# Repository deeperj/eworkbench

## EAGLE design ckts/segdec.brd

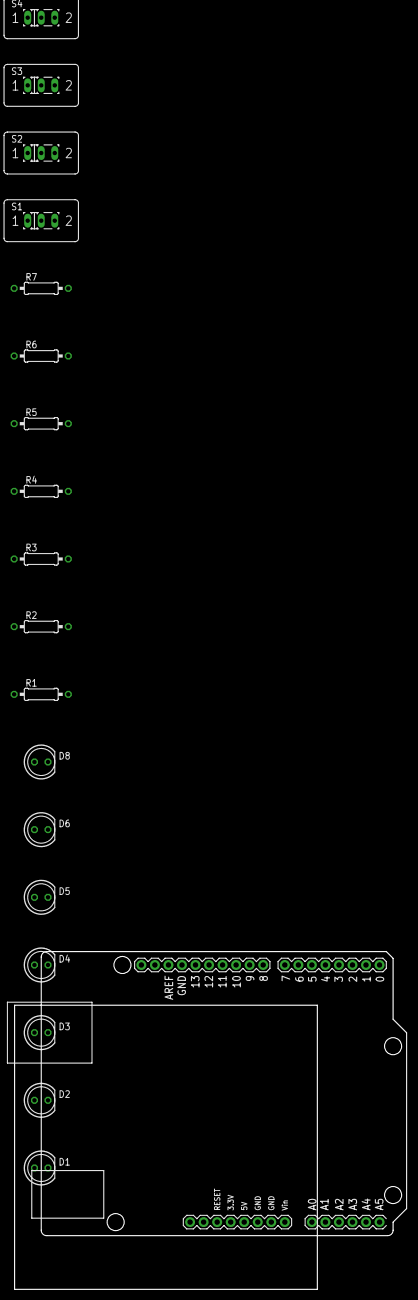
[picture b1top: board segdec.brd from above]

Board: 2 copper layers, 73.6 x 63.4 mm, 19 parts (0 on the bottom side), 20 nets, no tracks yet.

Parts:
D1, D2, D3, D4, D5, D6, D8: LED5MM
R1, R2, R3, R4, R5, R6, R7: 1k‎Ω; 0207/10
S1, S2, S3, S4: M251
U1: ARDUINO_UNO

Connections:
unnamed: D1.A, R1.2
unnamed: D4.A, R4.2
unnamed: S1.2, U1.13
unnamed: S2.2, U1.12
unnamed: S3.2, U1.11
unnamed: S4.2, U1.10
unnamed: S1.3, S2.3, S3.3, S4.3, U1.5V
unnamed: D8.A, R7.2
unnamed: D6.A, R6.2
unnamed: D5.A, R5.2
unnamed: D3.A, R3.2
unnamed: D2.A, R2.2
unnamed: D1.K, S1.1, S2.1, S3.1, S4.1, U1.GND.
unnamed: R7.1, U1.1
unnamed: R6.1, U1.2
unnamed: R5.1, U1.3
unnamed: R4.1, U1.4
unnamed: R3.1, U1.5
unnamed: R2.1, U1.6
unnamed: R1.1, U1.7

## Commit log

2019-03-09 sw_l053
2019-03-09 oscilloscope2.tft
2019-03-20 scomm
2019-03-20 working serial monitor driver
2019-03-21 std peripherals
2019-03-21 ignored help files
2019-03-21 serial comms complete
2019-03-21 TIMER funcs
2019-03-21 not quite sure what this is
2019-03-22 pause and capture implementation
2019-04-15 news00
2019-04-21 phantom zone
2019-04-21 superlists2
2019-04-21 ftesting
2019-04-22 agro
2019-04-22 dbpy00
2019-04-22 django_gen
2019-04-22 db00
2019-04-22 db01
2019-04-23 db02
2019-04-23 db03
2019-04-23 db04 dbpyv2
2019-04-23 dbx2yaml mgen refactor
2019-04-23 behave and stuff
2019-04-23 db04
2019-04-23 db05
2019-04-24 will cause a conflict
2019-04-24 modified beyond repair
2019-04-24 not a lot
2019-04-24 behave changes
2019-04-24 Agro app run
2019-04-24 not sure anymore
2019-05-01 ubl stuff
2019-05-01 python settings
2019-05-01 new bahave+models
2019-05-05 mods
2019-05-05 other mods
2019-05-09 forms
2019-05-13 tdel
2019-05-13 gitignore
2019-05-14 macsolutions
2019-05-15 gitck
2019-05-15 pvdata?
2019-05-15 mac2ann
2019-05-16 accuracy
2019-05-16 vsc mac python settings
2019-05-26 abcjade
2019-05-26 animate
2019-05-29 del macsol+agro_old
2019-05-29 award tender abcjade
2019-05-29 gignore
2019-05-29 gignore2
2019-05-29 what
2019-05-29 gignore3
2019-05-29 sync
2019-05-30 agro old
2019-06-05 weva
2019-06-07 design home
2019-06-11 element-vue-example
2019-06-23 mpp00
2019-06-23 ubl?
2019-09-07 whatever
2019-11-18 spice
2019-11-18 Bump lodash from 4.17.11 to 4.17.15 in /newngp/abcjade
    Bumps [lodash](https://github.com/lodash/lodash) from 4.17.11 to 4.17.15.
    - [Release notes](https://github.com/lodash/lodash/releases)
    - [Commits](https://github.com/lodash/lodash/compare/4.17.11...4.17.15)
2019-11-18 Bump mixin-deep from 1.3.1 to 1.3.2 in /newngp/abcjade
    Bumps [mixin-deep](https://github.com/jonschlinkert/mixin-deep) from 1.3.1 to 1.3.2.
    - [Release notes](https://github.com/jonschlinkert/mixin-deep/releases)
    - [Commits](https://github.com/jonschlinkert/mixin-deep/compare/1.3.1...1.3.2)
2019-12-28 Bump handlebars from 4.1.2 to 4.5.3 in /newngp/abcjade
    Bumps [handlebars](https://github.com/wycats/handlebars.js) from 4.1.2 to 4.5.3.
    - [Release notes](https://github.com/wycats/handlebars.js/releases)
    - [Changelog](https://github.com/wycats/handlebars.js/blob/master/release-notes.md)
    - [Commits](https://github.com/wycats/handlebars.js/compare/v4.1.2...v4.5.3)
2020-02-12 Bump django from 2.0 to 2.2.10 in /ftesting
    Bumps [django](https://github.com/django/django) from 2.0 to 2.2.10.
    - [Release notes](https://github.com/django/django/releases)
    - [Commits](https://github.com/django/django/compare/2.0...2.2.10)
2020-03-14 Bump acorn from 6.1.1 to 6.4.1 in /newngp/abcjade
    Bumps [acorn](https://github.com/acornjs/acorn) from 6.1.1 to 6.4.1.
    - [Release notes](https://github.com/acornjs/acorn/releases)
    - [Commits](https://github.com/acornjs/acorn/compare/6.1.1...6.4.1)
2020-04-16 Bump https-proxy-agent from 2.2.1 to 2.2.4 in /newngp/abcjade
    Bumps [https-proxy-agent](https://github.com/TooTallNate/node-https-proxy-agent) from 2.2.1 to 2.2.4.
    - [Release notes](https://github.com/TooTallNate/node-https-proxy-agent/releases)
    - [Commits](https://github.com/TooTallNate/node-https-proxy-agent/compare/2.2.1...2.2.4)
2020-06-05 Bump django from 2.0 to 2.2.13 in /ftesting
    Bumps [django](https://github.com/django/django) from 2.0 to 2.2.13.
    - [Release notes](https://github.com/django/django/releases)
    - [Commits](https://github.com/django/django/compare/2.0...2.2.13)
2020-06-06 Bump websocket-extensions from 0.1.3 to 0.1.4 in /newngp/abcjade
    Bumps [websocket-extensions](https://github.com/faye/websocket-extensions-node) from 0.1.3 to 0.1.4.
    - [Release notes](https://github.com/faye/websocket-extensions-node/releases)
    - [Changelog](https://github.com/faye/websocket-extensions-node/blob/master/CHANGELOG.md)
    - [Commits](https://github.com/faye/websocket-extensions-node/compare/0.1.3...0.1.4)
2020-07-17 Bump lodash from 4.17.11 to 4.17.19 in /newngp/abcjade
    Bumps [lodash](https://github.com/lodash/lodash) from 4.17.11 to 4.17.19.
    - [Release notes](https://github.com/lodash/lodash/releases)
    - [Commits](https://github.com/lodash/lodash/compare/4.17.11...4.17.19)
2020-07-30 Bump elliptic from 6.4.1 to 6.5.3 in /newngp/abcjade
    Bumps [elliptic](https://github.com/indutny/elliptic) from 6.4.1 to 6.5.3.
    - [Release notes](https://github.com/indutny/elliptic/releases)
    - [Commits](https://github.com/indutny/elliptic/compare/v6.4.1...v6.5.3)
2020-09-04 Bump node-sass from 4.9.2 to 4.13.1 in /newngp/element-vue-example
    Bumps [node-sass](https://github.com/sass/node-sass) from 4.9.2 to 4.13.1.
    - [Release notes](https://github.com/sass/node-sass/releases)
    - [Changelog](https://github.com/sass/node-sass/blob/master/CHANGELOG.md)
    - [Commits](https://github.com/sass/node-sass/compare/v4.9.2...v4.13.1)
2020-09-04 Bump handlebars from 4.1.2 to 4.7.6 in /newngp/abcjade
    Bumps [handlebars](https://github.com/wycats/handlebars.js) from 4.1.2 to 4.7.6.
    - [Release notes](https://github.com/wycats/handlebars.js/releases)
    - [Changelog](https://github.com/handlebars-lang/handlebars.js/blob/master/release-notes.md)
    - [Commits](https://github.com/wycats/handlebars.js/compare/v4.1.2...v4.7.6)
2020-09-09 Bump http-proxy from 1.17.0 to 1.18.1 in /newngp/abcjade
    Bumps [http-proxy](https://github.com/http-party/node-http-proxy) from 1.17.0 to 1.18.1.
    - [Release notes](https://github.com/http-party/node-http-proxy/releases)
    - [Changelog](https://github.com/http-party/node-http-proxy/blob/master/CHANGELOG.md)
    - [Commits](https://github.com/http-party/node-http-proxy/compare/1.17.0...1.18.1)
2020-09-22 cubik
2020-09-22 l0blinky
2020-09-22 usbtraining
2020-09-22 hid_term
2020-09-25 usbhid
2020-09-25 usb00
2020-09-28 stm01
2020-09-29 RTOS
2020-10-01 assy
2020-10-13 stm00
2020-11-02 mouseacc
2020-11-03 ld00
2021-03-09 Bump elliptic from 6.4.1 to 6.5.4 in /newngp/abcjade
    Bumps [elliptic](https://github.com/indutny/elliptic) from 6.4.1 to 6.5.4.
    - [Release notes](https://github.com/indutny/elliptic/releases)
    - [Commits](https://github.com/indutny/elliptic/compare/v6.4.1...v6.5.4)
2021-03-19 Bump djangorestframework from 3.6.2 to 3.11.2 in /ftesting
    Bumps [djangorestframework](https://github.com/encode/django-rest-framework) from 3.6.2 to 3.11.2.
    - [Release notes](https://github.com/encode/django-rest-framework/releases)
    - [Commits](https://github.com/encode/django-rest-framework/compare/3.6.2...3.11.2)
2021-03-19 Bump djangorestframework from 3.7.7 to 3.11.2 in /ftesting/agro
    Bumps [djangorestframework](https://github.com/encode/django-rest-framework) from 3.7.7 to 3.11.2.
    - [Release notes](https://github.com/encode/django-rest-framework/releases)
    - [Commits](https://github.com/encode/django-rest-framework/compare/3.7.7...3.11.2)
2021-03-30 Bump y18n from 3.2.1 to 3.2.2 in /newngp/abcjade
    Bumps [y18n](https://github.com/yargs/y18n) from 3.2.1 to 3.2.2.
    - [Release notes](https://github.com/yargs/y18n/releases)
    - [Changelog](https://github.com/yargs/y18n/blob/master/CHANGELOG.md)
    - [Commits](https://github.com/yargs/y18n/commits)
2021-05-07 Bump handlebars from 4.1.2 to 4.7.7 in /newngp/abcjade
    Bumps [handlebars](https://github.com/wycats/handlebars.js) from 4.1.2 to 4.7.7.
    - [Release notes](https://github.com/wycats/handlebars.js/releases)
    - [Changelog](https://github.com/handlebars-lang/handlebars.js/blob/master/release-notes.md)
    - [Commits](https://github.com/wycats/handlebars.js/compare/v4.1.2...v4.7.7)
2021-05-07 Bump url-parse from 1.4.7 to 1.5.1 in /newngp/abcjade
    Bumps [url-parse](https://github.com/unshiftio/url-parse) from 1.4.7 to 1.5.1.
    - [Release notes](https://github.com/unshiftio/url-parse/releases)
    - [Commits](https://github.com/unshiftio/url-parse/compare/1.4.7...1.5.1)
2021-05-08 Bump lodash from 4.17.11 to 4.17.21 in /newngp/abcjade
    Bumps [lodash](https://github.com/lodash/lodash) from 4.17.11 to 4.17.21.
    - [Release notes](https://github.com/lodash/lodash/releases)
    - [Commits](https://github.com/lodash/lodash/compare/4.17.11...4.17.21)
2021-05-10 Bump hosted-git-info from 2.7.1 to 2.8.9 in /newngp/abcjade
    Bumps [hosted-git-info](https://github.com/npm/hosted-git-info) from 2.7.1 to 2.8.9.
    - [Release notes](https://github.com/npm/hosted-git-info/releases)
    - [Changelog](https://github.com/npm/hosted-git-info/blob/v2.8.9/CHANGELOG.md)
    - [Commits](https://github.com/npm/hosted-git-info/compare/v2.7.1...v2.8.9)
2021-05-25 Bump browserslist from 4.6.0 to 4.16.6 in /newngp/abcjade
    Bumps [browserslist](https://github.com/browserslist/browserslist) from 4.6.0 to 4.16.6.
    - [Release notes](https://github.com/browserslist/browserslist/releases)
    - [Changelog](https://github.com/browserslist/browserslist/blob/main/CHANGELOG.md)
    - [Commits](https://github.com/browserslist/browserslist/compare/4.6.0...4.16.6)
2021-05-27 Bump dns-packet from 1.3.1 to 1.3.4 in /newngp/abcjade
    Bumps [dns-packet](https://github.com/mafintosh/dns-packet) from 1.3.1 to 1.3.4.
    - [Release notes](https://github.com/mafintosh/dns-packet/releases)
    - [Changelog](https://github.com/mafintosh/dns-packet/blob/master/CHANGELOG.md)
    - [Commits](https://github.com/mafintosh/dns-packet/compare/v1.3.1...v1.3.4)
2021-06-10 Bump django from 2.0 to 2.2.24 in /ftesting
    Bumps [django](https://github.com/django/django) from 2.0 to 2.2.24.
    - [Release notes](https://github.com/django/django/releases)
    - [Commits](https://github.com/django/django/compare/2.0...2.2.24)
    ---
    updated-dependencies:
    - dependency-name: django
2021-07-01 asio_reset00
2021-07-02 reset01
